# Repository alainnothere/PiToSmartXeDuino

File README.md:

# PiToSmartXeDuino

Turn a forgotten classroom gadget into a portable Linux terminal.
I have always liked those mono lcd pixelated displays and had to do something with this one.

## What is This?

Remember those clicker devices schools used for quizzes? The SMART Response XE was one of them - a handheld unit with a full QWERTY keyboard and a monochrome screen that students used to answer questions. They were discontinued years ago and thousands ended up in surplus bins.
This project gives them new life by converting a SMART Response XE into a hardware terminal for a Raspberry Pi Zero 2W. You type commands on the XE's keyboard, see output on its screen, and the Pi does all the computing. It's a self-contained, battery-powered Linux terminal that fits in your hand.

This project wants to turn those SMART XE into a keyboard/display shield for the Raspberry Pi Zero 2w.

## Why Would You Want This?

**Nostalgia**: Remember when computers had actual keyboards attached and weren't just touchscreens?

**Portability**: A complete Linux system with a physical keyboard that runs for hours on AA batteries.

**Learning**: It's a fantastic way to learn about serial protocols, embedded systems, and creative hardware reuse.

**Fun**: Because making old hardware do new tricks and be able to repurposed them and give them new life it's fun!.

## What Does It Do?

In practical terms:
- Type commands on the XE keyboard → they appear on the XE screen
- Press enter → command runs on the Pi
- Output displays on the XE screen
- Switch between 4 different font sizes on the fly
- Scroll through command history
- All the power of Linux in your pocket

Think of it as a vintage-looking cyberdeck, or a Game Boy that runs bash.

## The Technical Bit (Overview)

If you're curious about how this works under the hood:

**Hardware**: The Raspberry Pi Zero 2W connects to the SMART Response XE through an adapter board that plugs into the XE's JTAG header (the pins on the back normally used for firmware updates). No modifications to the XE itself are needed - the adapter board replaces the battery cover.

**Communication**: The two devices talk using a software-implemented serial protocol at 19,200 baud. The Pi uses the hardware serial port pins and the `pigpio` library to read a flag set by the Arduino to let the pi know it's ready to receive data, while the Arduino-based XE bitbangs serial data through its JTAG pins (TDO, TCK, TMS, TDI it's free for you to use it and connected to pin 37 on the Pi).

**Division of Labor**: The XE is a "dumb terminal" - it only handles keyboard scanning and screen rendering. The Pi runs all the actual commands, manages the terminal buffer, and decides what to display. This keeps the XE's ATmega128RFA1 microcontroller focused on what it does best: presenting text and capturing the keys.

**Optimization**: Instead of sending every keystroke individually (which would be slow), the XE buffers an entire command line locally, showing you what you type with a blinking cursor, and only sends the complete line when you press Enter. The Pi then executes the command and sends back only the screen lines that changed.

## Current Status

**What works:**
- Full keyboard input with modifier keys (Shift, Sym)
- Terminal emulation (bash, most CLI programs)
- Four font sizes (52x17, 64x17, 32x8, 25x8 characters)
- Command execution with output display
- Screen scrolling
- Efficient differential screen updates
- Buffered line input (reduced round-trips)

**What doesn't work yet:**
- Full-screen terminal applications (nano, vim, top) - these need proper VT100 escape sequence handling
- Special characters/graphics that don't fit in the limited font

**Known quirks:**
- The XE keyboard matrix is tied to the hardware serial pins, so we use software serial on the JTAG pins instead
- Some XE units have noisy keyboards (filtering implemented)
- Font switching clears the screen (by design - different layouts)

## Quick Hardware Overview

```
┌─────────────────────────────────┐
│   SMART Response XE             │
│  ┌──────────────────────────┐   │
│  │  384x136 LCD Screen      │   │
│  └──────────────────────────┘   │
│                                  │
│  [QWERTY Keyboard Layout]        │
│                                  │
│  ATmega128RFA1 MCU               │
│                                  │
│  ┌────────────────┐              │
│  │ JTAG Header    │              │
│  │ (TDO/TCK/TMS)  │              │
│  └────────┬───────┘              │
└───────────┼──────────────────────┘
            │
            │  Soft Serial @ 19200 baud
            │  (3 wires: TX, RX, Signal)
            │
      ┌─────▼──────────────────────┐
      │  Adapter Board              │
      │  (replaces battery cover)   │
      └─────┬──────────────────────┘
            │
            │  40-pin GPIO connector
            │
      ┌─────▼──────────────────────┐
      │  Raspberry Pi Zero 2W       │
      │                             │
      │  - Runs Python terminal     │
      │  - Executes commands        │
      │  - Manages screen buffer    │
      │  - 512MB RAM, quad-core     │
      └─────────────────────────────┘
```

## Project Philosophy

This project embraces the "boring technology" philosophy:
- **Pi side**: Python with standard libraries (serial, subprocess, no exotic dependencies)
- **Arduino side**: Plain C++ with minimal libraries
- **Protocol**: Simple packet-based serial communication with checksums
- **Screen library**: Built on bitbank2's excellent SmartResponseXE library

The goal is reliability and understandability over cleverness, but I had to make use of CLAUDE to optimize the duino side to get the serial speed to 19200, using typical read/write I was able to get to 4800 and nothing more. You should be able to read the code, understand what it does, and fix it when it breaks.

## Next Steps

If you want to build one of these, jump to:
- **[Hardware Setup](docs/HARDWARE.md)** - Wiring and assembly
- **[Installation](docs/INSTALLATION.md)** - Software setup
- **[Usage Guide](docs/USAGE.md)** - How to use it

If you want to understand how it works:
- **[Architecture](docs/ARCHITECTURE.md)** - System design
- **[Protocol Specification](docs/PROTOCOL.md)** - Communication details
- **[Development Guide](docs/DEVELOPMENT.md)** - Contributing

## Credits

This project builds on the work of many people who've documented and hacked the SMART Response XE platform:

- **bitbank2** - [SmartResponseXE library](https://github.com/bitbank2/SmartResponseXE) that makes the screen work and reads the keyboard.
- The SMART Response XE community - Years of documentation on the hardware
- **Larry Bank** - Original XE reverse engineering work

The adapter board design, soft serial implementation, terminal protocol, and integration are original to this project.

## License

GPL-3.0 - See LICENSE file for details.

---

*"please document what you do with all this info so in the future some poor soul that decides to work on this have this info"* - Comment found in the code

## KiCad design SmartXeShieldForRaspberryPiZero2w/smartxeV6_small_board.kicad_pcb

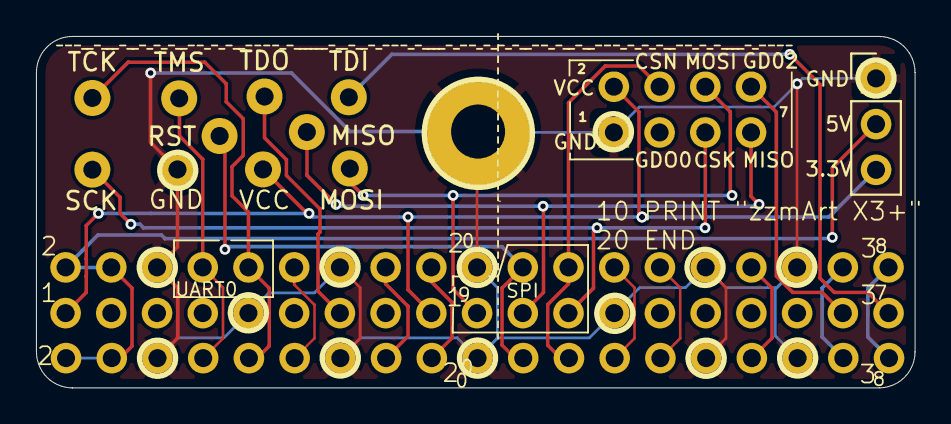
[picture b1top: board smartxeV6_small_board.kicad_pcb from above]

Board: 2 copper layers, 48.8 x 19.5 mm, 11 parts (0 on the bottom side), 11 nets.

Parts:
GND: SolderWire-1.5sqmm_1x01_D1.7mm_OD3.9mm
MISO: SolderWire-1.5sqmm_1x01_D1.7mm_OD3.9mm
MOSI: SolderWire-1.5sqmm_1x01_D1.7mm_OD3.9mm
RST: SolderWire-1.5sqmm_1x01_D1.7mm_OD3.9mm
SCK: SolderWire-1.5sqmm_1x01_D1.7mm_OD3.9mm
TCK: SolderWire-1.5sqmm_1x01_D1.7mm_OD3.9mm
TDI: SolderWire-1.5sqmm_1x01_D1.7mm_OD3.9mm
TDO: SolderWire-1.5sqmm_1x01_D1.7mm_OD3.9mm
TMS: SolderWire-1.5sqmm_1x01_D1.7mm_OD3.9mm
VCC: SolderWire-1.5sqmm_1x01_D1.7mm_OD3.9mm
_: Raspberry_Pi_Zero_Socketed_THT_FaceDown_MountingH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; Raspberry_Pi_Zero_Socketed_THT_FaceDown_MountingHoles

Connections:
GND: GND.GND, _.6_GND, _.9, _.14_GND, _.20_GND, _.25_GND, _.30_GND, _.34_GND
MISO_PI: MISO.MISO, _.MISO_PI
MOSI_PI: MOSI.MOSI, _.MOSI_PI
RST_DUINO: RST.RST, _.GPIO25 PI_RESET
SCK_PI: SCK.SCK, _.SCK_PI
TCK_TO_TX_DUINO: TCK.TCK_CSN_DUINO, _.10
TDI: TDI.TDI, _.37
TDO_SIGNAL_TO_TRANSFER_TO_DUINO: TDO.TDO, _.13
TMS_TO_RX_DUINO: TMS.TMS, _.8
VCC: VCC.VCC, _.1_3V, _.17_3V3
VCC_5V: _.2_5V, _.4_5V

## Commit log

2025-10-16 Create ArduinoSide folder
2025-10-16 Create RaspeberryPiSide folder
2025-10-16 Create test
2025-10-16 Create s
2025-12-26 Updating to the latest version of the code, renaming folders
2025-12-26 updating the documentation
2025-12-26 creating folder for the old approach when opening the XE
2025-12-26 adding more photos of the board and how it looks the adapter on the smart xe
2025-12-26 update md file with photos
2025-12-27 adding Installation.md, adding scripts to install, flash, and run
